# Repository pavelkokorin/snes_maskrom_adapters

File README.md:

# SNES/SFC Maskrom Adapters

## PSOP to DIP adapters
Adapters to replace SNES DIP32/DIP36 maskrom with PSOP44 Flash.

### snes_maskrom_psop_to_dip_adapter
Backside PSOP44 to DIP36 adapter. Designed and tested for MX29F1610. Non destructive option, CE\`/OE\` pins of original maskrom should be cut.

### snes_maskrom_psop_to_dip_adapter_front
Fronside PSOP44 to DIP36 adapter. Designed and tested for MX29F1610. Replaces original maskrom.

## TSOP to DIP adapters
Adapters to replace SNES DIP32/DIP36 maskrom with TSOP40/TSOP48 Flash.

## snes_maskrom_tsop_to_dip_adapter
Backside TSOP40/TSOP48 to DIP36 adapter. Designed and tested for 29F032/29F033. Replaces original maskrom. Non destructive option, CE\`/OE\` pins of original maskrom should be cut.

## snes_maskrom_tsop_to_fx_adapter
Adapters to replace SNES PSOP36/PSOP42 maskrom with TSOP40/TSOP48 Flash.

Maskroms: MX23C1601-12, M531610D-20, UPD23C4013 and other similar maskrom ICs.

Inspired by https://github.com/retrostage/SNES-SuperFX-adapter project.
Redesigned in KiCad to use less expensive production process, added some test points (WE#, RST#) for inschematic programming ability.

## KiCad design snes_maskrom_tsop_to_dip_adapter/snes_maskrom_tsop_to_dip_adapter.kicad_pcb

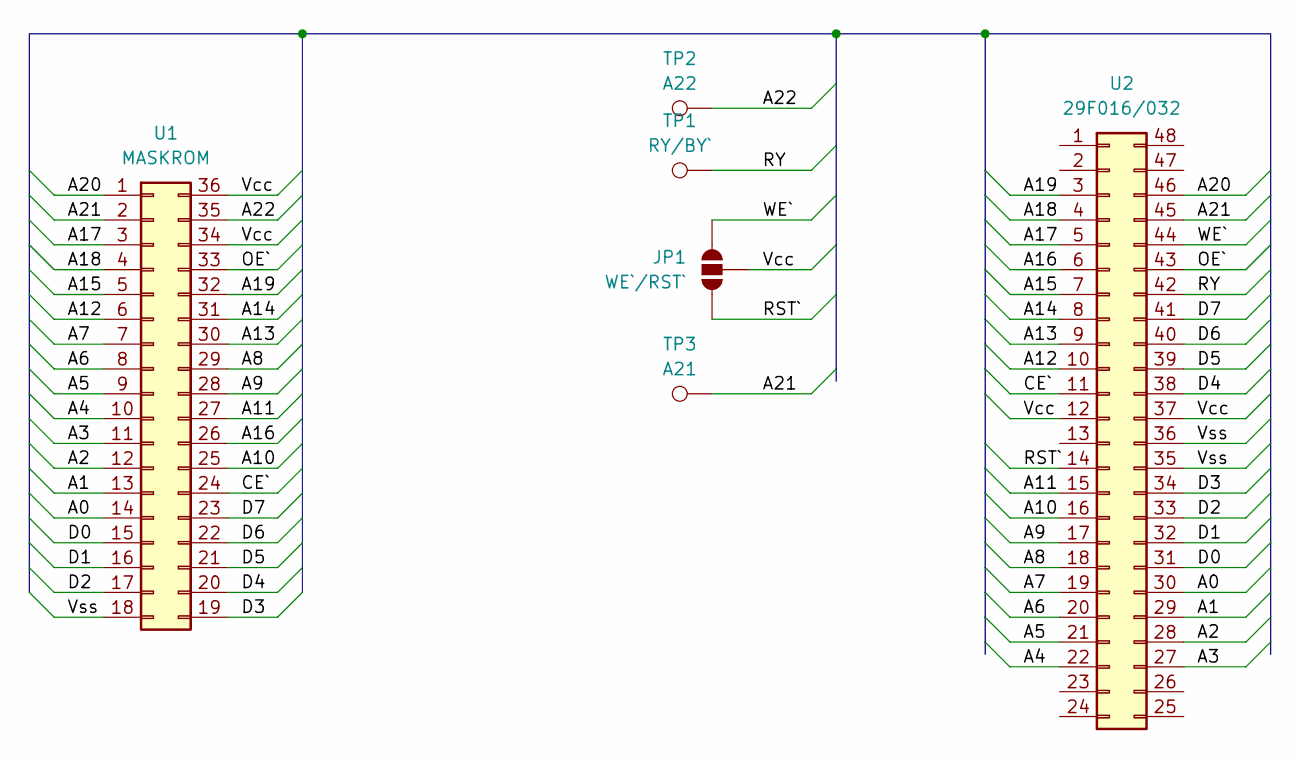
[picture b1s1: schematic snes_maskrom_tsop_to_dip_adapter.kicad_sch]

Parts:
JP1: WE`/RST`; SolderJumper-3_P1.3mm_Open_RoundedPad1.0x1.5mm_NumberLabels
TP1: RY/BY`; TestPoint_Pad_D1.0mm
TP2: A22; TestPoint_Pad_D1.0mm
TP3: A21; TestPoint_Pad_D1.0mm
U1: MASKROM; DIP-36_W15.24mm
U2: 29F016/032; TSOP-I-48_18.4x12mm_P0.5mm

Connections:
/A0: U1.14, U2.30
/A1: U1.13, U2.29
/A2: U1.12, U2.28
/A3: U1.11, U2.27
/A4: U1.10, U2.22
/A5: U1.9, U2.21
/A6: U1.8, U2.20
/A7: U1.7, U2.19
/A8: U1.29, U2.18
/A9: U1.28, U2.17
/A10: U1.25, U2.16
/A11: U1.27, U2.15
/A12: U1.6, U2.10
/A13: U1.30, U2.9
/A14: U1.31, U2.8
/A15: U1.5, U2.7
/A16: U1.26, U2.6
/A17: U1.3, U2.5
/A18: U1.4, U2.4
/A19: U1.32, U2.3
/A20: U1.1, U2.46
/A21: TP3.1, U1.2, U2.45
/A22: TP2.1, U1.35
/CE`: U1.24, U2.11
/D0: U1.15, U2.31
/D1: U1.16, U2.32
/D2: U1.17, U2.33
/D3: U1.19, U2.34
/D4: U1.20, U2.38
/D5: U1.21, U2.39
/D6: U1.22, U2.40
/D7: U1.23, U2.41
/OE`: U1.33, U2.43
/RST`: JP1.1 (A), U2.14
/RY: TP1.1, U2.42
/Vcc: JP1.2 (C), U1.34, U1.36, U2.12, U2.37
/Vss: U1.18, U2.35, U2.36
/WE`: JP1.3 (B), U2.44

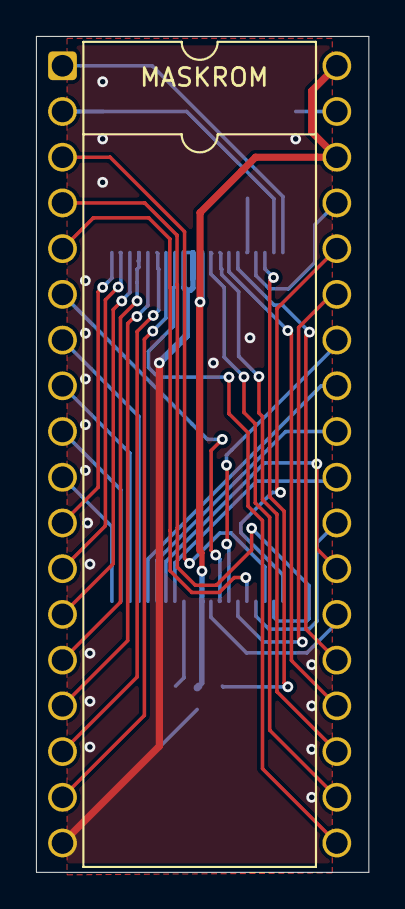
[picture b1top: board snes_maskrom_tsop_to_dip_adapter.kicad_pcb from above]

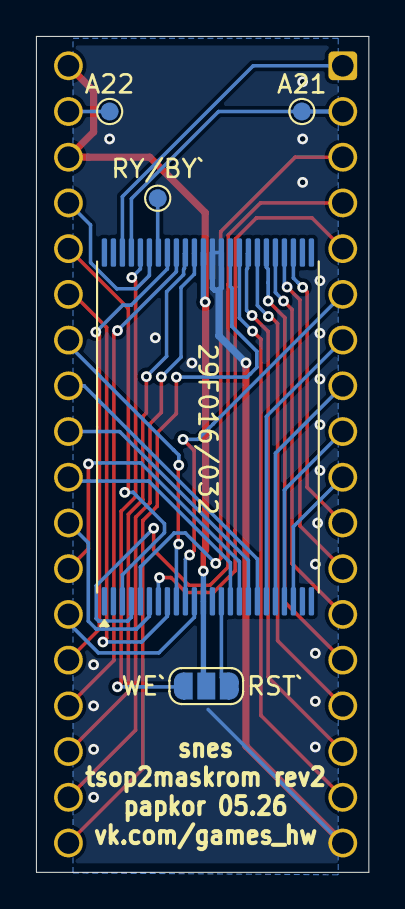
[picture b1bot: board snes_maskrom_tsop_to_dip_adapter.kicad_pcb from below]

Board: 2 copper layers, 18.5 x 46.4 mm, 6 parts (5 on the bottom side), 38 nets.

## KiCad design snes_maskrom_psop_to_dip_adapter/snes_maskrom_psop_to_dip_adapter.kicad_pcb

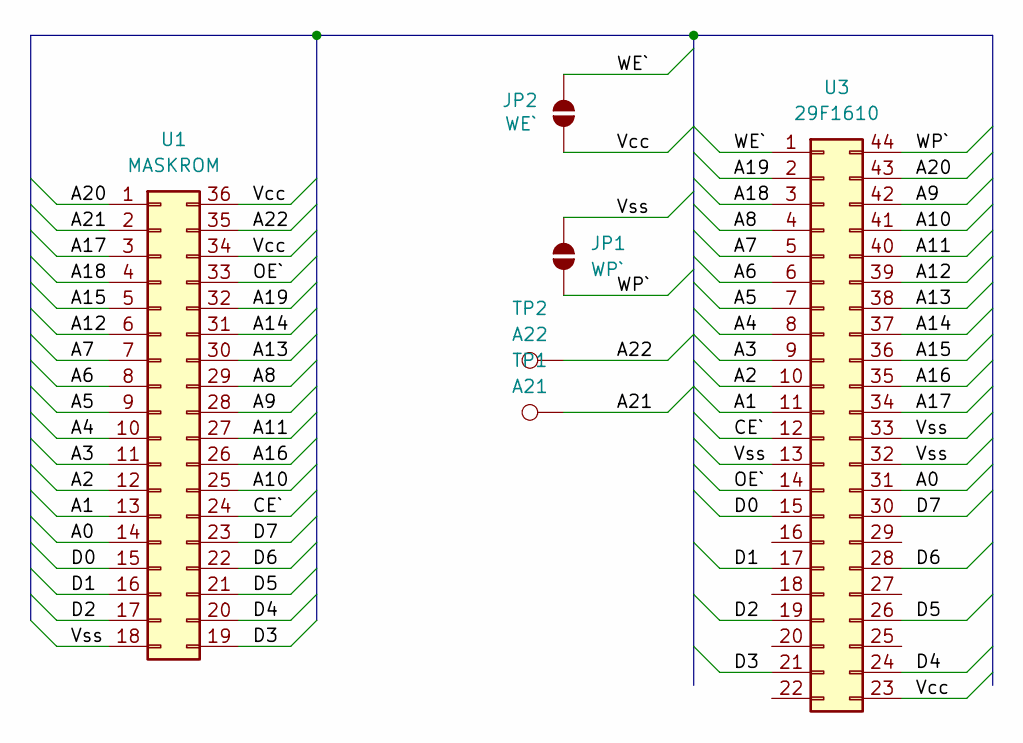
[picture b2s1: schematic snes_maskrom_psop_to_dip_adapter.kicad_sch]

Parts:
JP1: WP`; SolderJumper-2_P1.3mm_Open_RoundedPad1.0x1.5mm
JP2: WE`; SolderJumper-2_P1.3mm_Open_RoundedPad1.0x1.5mm
TP1: A21; TestPoint_Pad_D1.0mm
TP2: A22; TestPoint_Pad_D1.0mm
U1: MASKROM; DIP-36_W15.24mm
U3: 29F1610; SOP-44_12.6x28.5mm_P1.27mm

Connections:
/A0: U1.14, U3.31
/A1: U1.13, U3.11
/A2: U1.12, U3.10
/A3: U1.11, U3.9
/A4: U1.10, U3.8
/A5: U1.9, U3.7
/A6: U1.8, U3.6
/A7: U1.7, U3.5
/A8: U1.29, U3.4
/A9: U1.28, U3.42
/A10: U1.25, U3.41
/A11: U1.27, U3.40
/A12: U1.6, U3.39
/A13: U1.30, U3.38
/A14: U1.31, U3.37
/A15: U1.5, U3.36
/A16: U1.26, U3.35
/A17: U1.3, U3.34
/A18: U1.4, U3.3
/A19: U1.32, U3.2
/A20: U1.1, U3.43
/A21: TP1.1, U1.2
/A22: TP2.1, U1.35
/CE`: U1.24, U3.12
/D0: U1.15, U3.15
/D1: U1.16, U3.17
/D2: U1.17, U3.19
/D3: U1.19, U3.21
/D4: U1.20, U3.24
/D5: U1.21, U3.26
/D6: U1.22, U3.28
/D7: U1.23, U3.30
/OE`: U1.33, U3.14
/Vcc: JP2.1 (A), U1.34, U1.36, U3.23
/Vss: JP1.2 (B), U1.18, U3.13, U3.32, U3.33
/WE`: JP2.2 (B), U3.1
/WP`: JP1.1 (A), U3.44

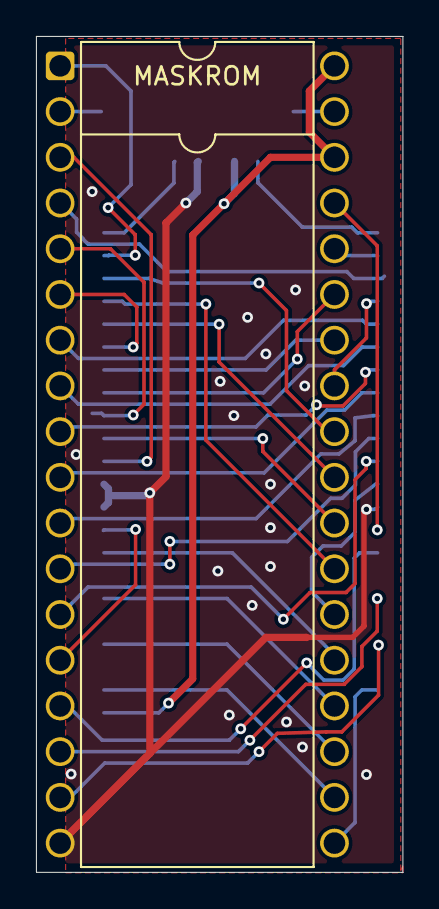
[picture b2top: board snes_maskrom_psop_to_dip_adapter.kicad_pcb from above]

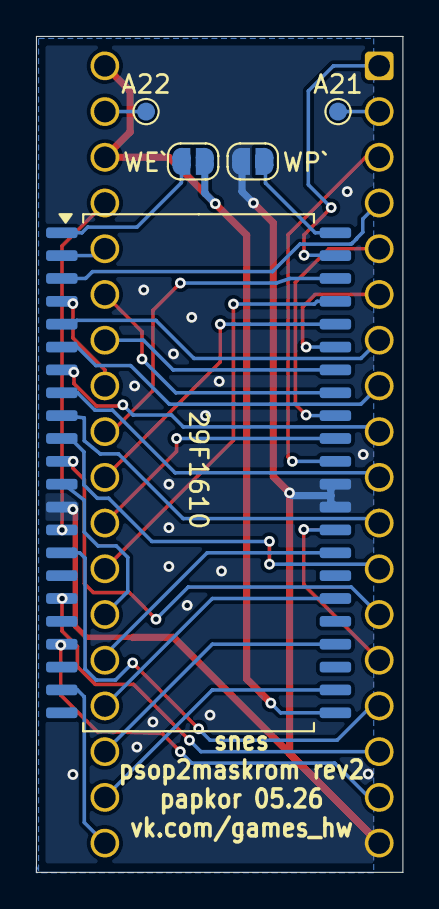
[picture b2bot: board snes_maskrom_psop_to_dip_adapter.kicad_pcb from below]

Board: 2 copper layers, 20.4 x 46.4 mm, 6 parts (5 on the bottom side), 37 nets.

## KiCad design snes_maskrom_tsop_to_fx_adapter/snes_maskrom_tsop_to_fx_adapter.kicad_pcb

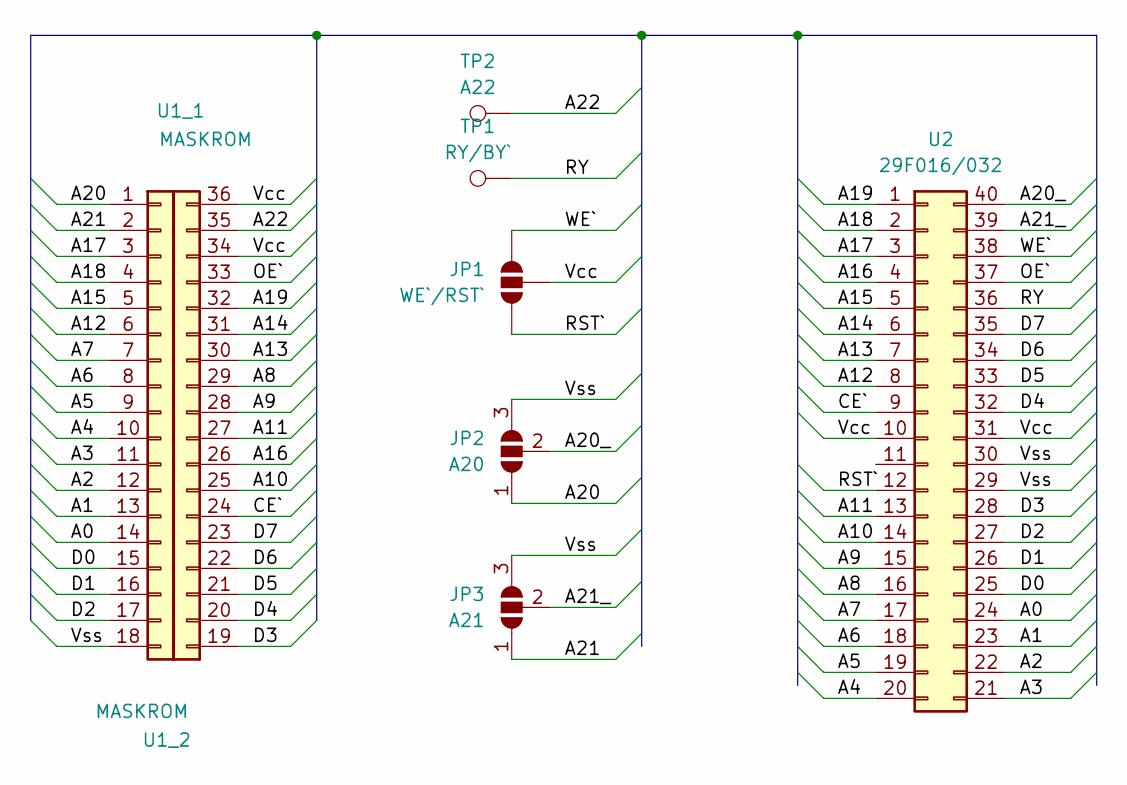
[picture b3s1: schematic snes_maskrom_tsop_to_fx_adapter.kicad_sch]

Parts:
JP1: WE`/RST`; SolderJumper-3_P1.3mm_Bridged123_Pad1.0x1.5mm_NumberLabels
JP2: A20; SolderJumper-3_P1.3mm_Bridged12_Pad1.0x1.5mm_NumberLabels
JP3: A21; SolderJumper-3_P1.3mm_Bridged12_Pad1.0x1.5mm_NumberLabels
TP1: RY/BY`; TestPoint_Pad_D1.0mm
TP2: A22; TestPoint_Pad_D1.0mm
U1_1, U1_2: MASKROM; PinHeader_1x18_P1.27mm_Vertical
U2: 29F016/032; TSOP-I-40_18.4x10mm_P0.5mm

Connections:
/A0: U1_1.14, U2.24
/A1: U1_1.13, U2.23
/A2: U1_1.12, U2.22
/A3: U1_1.11, U2.21
/A4: U1_1.10, U2.20
/A5: U1_1.9, U2.19
/A6: U1_1.8, U2.18
/A7: U1_1.7, U2.17
/A8: U1_2.29, U2.16
/A9: U1_2.28, U2.15
/A10: U1_2.25, U2.14
/A11: U1_2.27, U2.13
/A12: U1_1.6, U2.8
/A13: U1_2.30, U2.7
/A14: U1_2.31, U2.6
/A15: U1_1.5, U2.5
/A16: U1_2.26, U2.4
/A17: U1_1.3, U2.3
/A18: U1_1.4, U2.2
/A19: U1_2.32, U2.1
/A20: JP2.1 (A), U1_1.1
/A20_: JP2.2 (C), U2.40
/A21: JP3.1 (A), U1_1.2
/A21_: JP3.2 (C), U2.39
/A22: TP2.1, U1_2.35
/CE`: U1_2.24, U2.9
/D0: U1_1.15, U2.25
/D1: U1_1.16, U2.26
/D2: U1_1.17, U2.27
/D3: U1_2.19, U2.28
/D4: U1_2.20, U2.32
/D5: U1_2.21, U2.33
/D6: U1_2.22, U2.34
/D7: U1_2.23, U2.35
/OE`: U1_2.33, U2.37
/RST`: JP1.1 (A), U2.12
/RY: TP1.1, U2.36
/Vcc: JP1.2 (C), U1_2.34, U1_2.36, U2.10, U2.31
/Vss: JP2.3 (B), JP3.3 (B), U1_1.18, U2.29, U2.30
/WE`: JP1.3 (B), U2.38

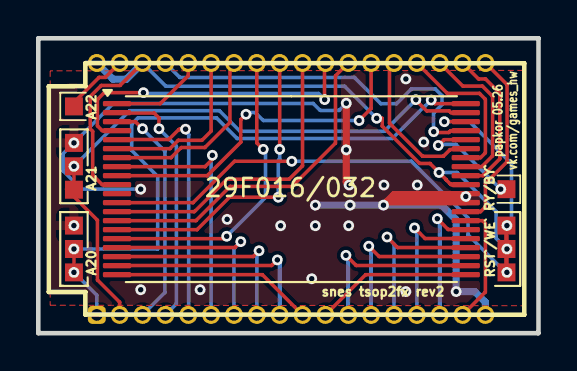
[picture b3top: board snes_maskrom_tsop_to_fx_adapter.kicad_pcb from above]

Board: 2 copper layers, 27.8 x 16.4 mm, 8 parts (0 on the bottom side), 40 nets.

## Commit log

2025-08-26 Added snes psop to dip adapters
2025-08-26 add README and images
2025-08-26 add README and images@
2025-08-26 change readme.me
2025-08-27 update README and images
2025-08-27 update images resolution
2025-11-27 added snes_maskrom_tsop_to_fx_adapter
2025-11-27 pix resize
2026-05-04 added snes_maskrom_tsop_to_dip_adapter
2026-05-04 added snes_maskrom_tsop_to_dip_adapter fix
2026-05-17 update img and gerbers
2026-05-17 fix README.md
2026-05-17 fix img resx
